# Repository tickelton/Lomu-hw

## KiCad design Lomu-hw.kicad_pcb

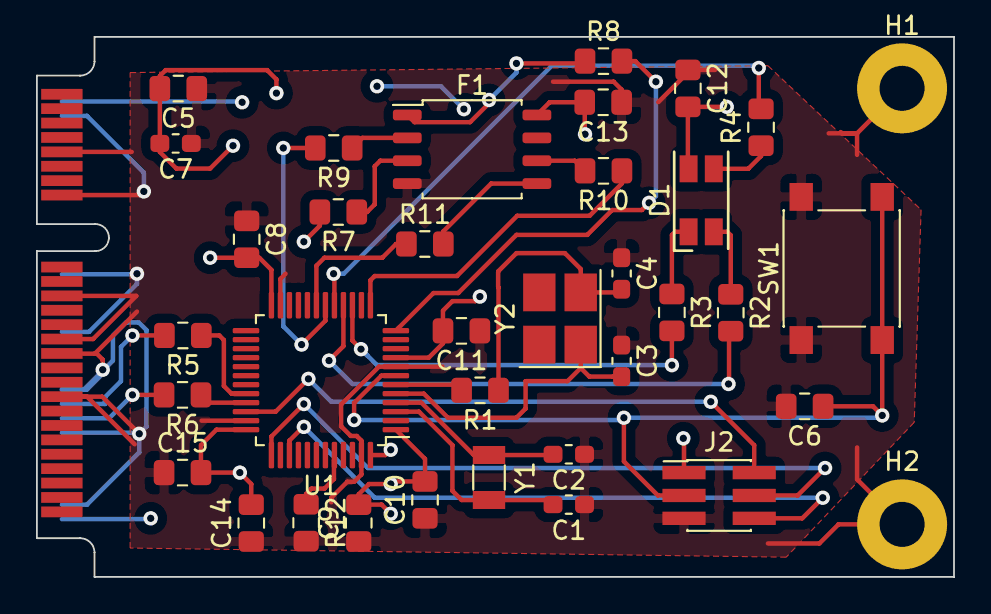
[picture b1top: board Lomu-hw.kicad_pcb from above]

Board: 2 copper layers, 50.9 x 30.0 mm, 37 parts (0 on the bottom side), 31 nets.

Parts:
C1, C2: 10pF; C_0603_1608Metric_Pad1.05x0.95mm_HandSolder
C3, C4: 20pF; C_0603_1608Metric_Pad1.05x0.95mm_HandSolder
C5, C6, C8, C9, C10, C11, C12, C13, C15: 100nF; C_0805_2012Metric_Pad1.15x1.40mm_HandSolder
C7: 47pF; C_0603_1608Metric_Pad1.05x0.95mm_HandSolder
C14: 4.7uF; C_0805_2012Metric_Pad1.15x1.40mm_HandSolder
D1: LED_RGBA; LED_RGB_1210
F1: MX25V1606FM2I03; SOP-8_5.28x5.23mm_P1.27mm
H1, H2: MountingHole_Pad; MountingHole_2.5mm_Pad
J1: PCIE-MINI; miniPCIeConn
J2: ARM_SWD_6; PinHeader_2x03_P1.27mm_Vertical_SMD
R1: 390; R_0805_2012Metric_Pad1.15x1.40mm_HandSolder
R2, R4: 1; R_0805_2012Metric_Pad1.15x1.40mm_HandSolder
R3: 68; R_0805_2012Metric_Pad1.15x1.40mm_HandSolder
R5, R6: 22; R_0805_2012Metric_Pad1.15x1.40mm_HandSolder
R7, R12: 10k; R_0805_2012Metric_Pad1.15x1.40mm_HandSolder
R8, R9, R10, R11: 33; R_0805_2012Metric_Pad1.15x1.40mm_HandSolder
SW1: SW_Push_Dual; SW_Push_1P1T_NO_6x6mm_H9.5mm
U1: STM32L562CET6; LQFP-48_7x7mm_P0.5mm
Y1: 32 kHz; Crystal_SMD_3215-2Pin_3.2x1.5mm
Y2: 16 MHz; Crystal_SMD_3225-4Pin_3.2x2.5mm_HandSoldering

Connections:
/LED1: R3.2, U1.15
/LED2: R2.2, U1.16
/LED3: R4.2, U1.17
/NRST: C6.1, J2.3, SW1.2, U1.7
/OCTOSPI1_CLK: R10.1, U1.13
/OCTOSPI1_IO0: R11.1, U1.19
/OCTOSPI1_IO1: R9.2, U1.18
/OCTOSPI1_NCS: R8.2, U1.12
/OSC32_IN: C1.2, U1.3, Y1.1
/OSC32_OUT: C2.2, U1.4, Y1.2
/OSC_IN: C3.2, U1.5, Y2.1
/OSC_OUT: R1.2, U1.6
/TCK_SWCLK: J2.4, U1.37
/TDO_SWO: J2.6, U1.39
/TMS_SWDIO: J2.2, U1.34
/USB_D+: R6.1, U1.33
/USB_D-: R5.1, U1.32
GND: C1.1, C2.1, C3.1, C4.1, C5.1, C6.2, C7.1, C8.1, C9.1, C10.1, C11.1, C12.1, C13.1, C14.1, C15.1, F1.4, H1.1, H2.1, J1.4, J1.9, J1.15, J1.18, J1.21, J1.26, J1.27, J1.29, J1.34, J1.35, J1.40, J1.50, J2.5, R12.2, SW1.1, U1.8, U1.23, U1.35, U1.47
unnamed: C4.2, R1.1, Y2.2
unnamed: D1.1, R3.1
unnamed: D1.2, R2.1
unnamed: D1.3, R4.1
unnamed: F1.1, R8.1
unnamed: F1.2, R9.1
unnamed: F1.3, R7.1
unnamed: F1.5, R11.2
unnamed: F1.6, R10.2
unnamed: J1.36, R5.2
unnamed: J1.38, R6.2
unnamed: R12.1, U1.44
VCC: C5.2, C7.2, C8.2, C9.2, C10.2, C11.2, C12.2, C13.2, C14.2, C15.2, D1.4, F1.8, J1.2, J1.52, J2.1, R7.2, U1.1, U1.9, U1.24, U1.36, U1.48

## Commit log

2021-02-12 Adds .gitignore
2021-02-12 Adds STM32L552CCT6 to library
2021-02-17 Updates project from mPCIe F1 template
2021-02-18 Adds crystals and LED
2021-02-18 Adds remaining components
2021-02-21 Adds annotations
2021-02-21 Adds first draft of layout
2021-02-22 Adds gerber files
2021-02-24 Adds pdf schematic and PCB renderings
2021-03-04 Adds photo of actual PCB
2021-03-12 Adds picture of populated PCB
2021-06-21 Adds missing boot select trace
2021-06-22 Updates PDF
    The PDF plot is now in sync again with the schematic
    and includes the missing boot select trace and pull
    down resistor.
